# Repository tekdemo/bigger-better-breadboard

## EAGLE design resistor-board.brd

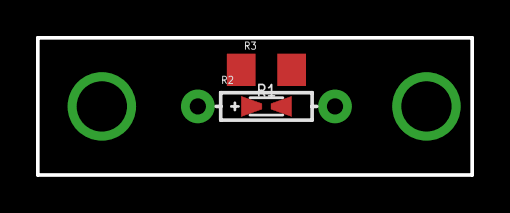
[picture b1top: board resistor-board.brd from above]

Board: 2 copper layers, 24.1 x 7.6 mm, 3 parts (0 on the bottom side), 2 nets, no tracks yet.

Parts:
R1: 0402-0603-0805-UNIVERSAL
R2: AXIAL-0.3
R3: 1206

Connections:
unnamed: R1.-, R2.P$2, R3.2
unnamed: R1.+, R2.P$1, R3.1
